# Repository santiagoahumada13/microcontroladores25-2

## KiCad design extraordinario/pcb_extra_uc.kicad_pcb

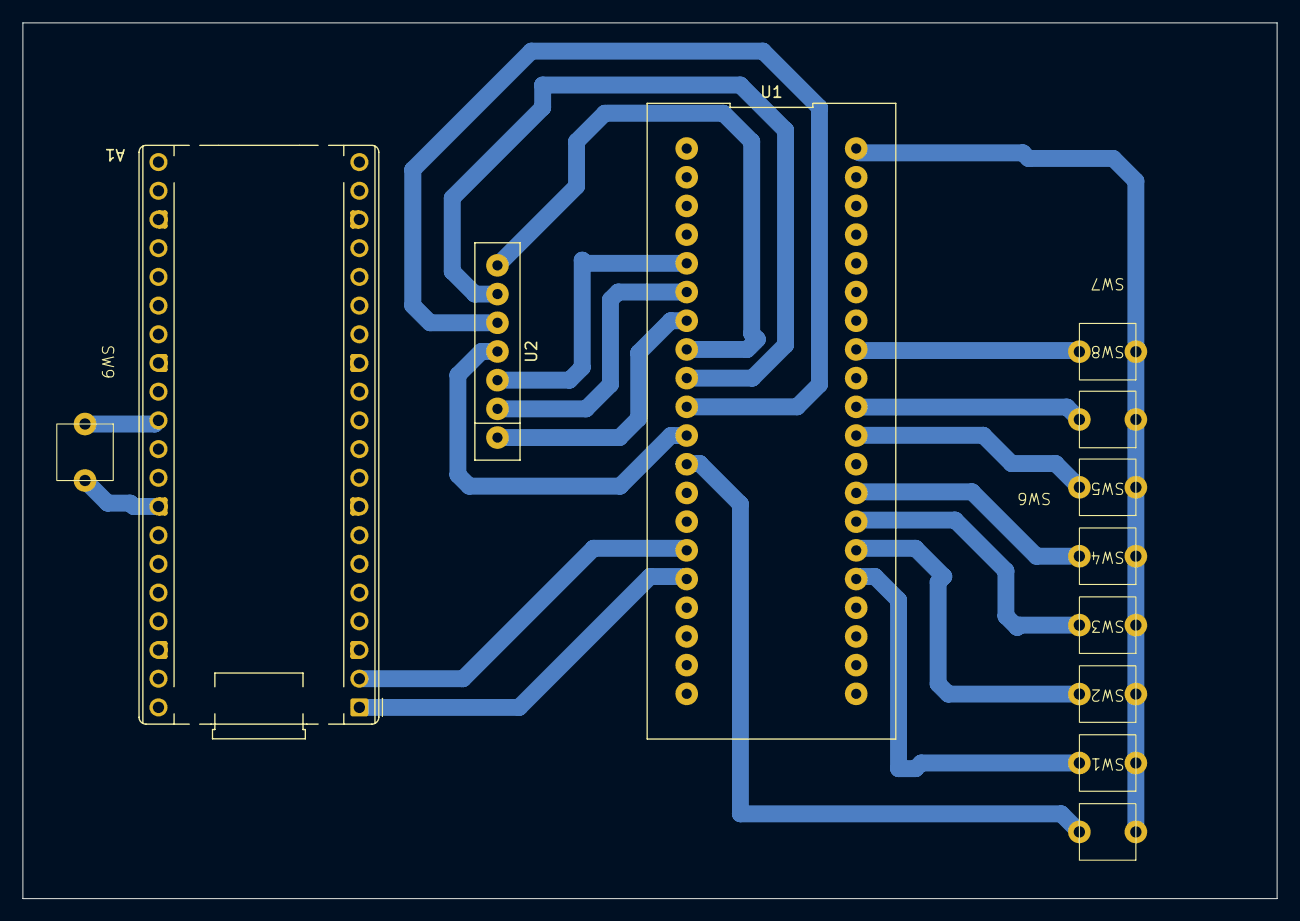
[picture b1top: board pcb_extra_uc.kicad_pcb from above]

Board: 2 copper layers, 111.0 x 77.5 mm, 12 parts (0 on the bottom side), 21 nets.

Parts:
A1: RaspberryPi_Pico_W; RaspberryPi_Pico_Common_THT
SW1, SW2, SW3, SW4, SW5, SW6, SW7, SW8, SW9: SW_Push; push_bttn2x1-tht
U1: STM32F104C8T6 BluePill
U2: keypad4x3

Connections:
unnamed: A1.33 (AGND), SW9.1
unnamed: A1.3 (GND), A1.8 (GND), A1.13 (GND), A1.18 (GND), A1.23 (GND), A1.28 (GND), A1.38 (GND)
unnamed: A1.1 (GPIO0), U1.16 (B11)
unnamed: A1.2 (GPIO1), U1.15 (B10)
unnamed: A1.30 (RUN), SW9.2
unnamed: SW1.2, SW2.2, SW3.2, SW4.2, SW5.2, SW6.2, SW7.2, SW8.2, U1.40 (3.3)
unnamed: U1.5 (A0), U2.3 (R3)
unnamed: U1.6 (A1), U2.2 (R2)
unnamed: U1.7 (A2), U2.1 (R1)
unnamed: U1.8 (A3), U2.7 (C3)
unnamed: U1.9 (A4), U2.6 (C2)
unnamed: U1.10 (A5), U2.5 (C1)
unnamed: U1.11 (A6), U2.4 (R4)
unnamed: SW1.1, U1.12 (A7)
unnamed: SW2.1, U1.25 (A8)
unnamed: SW3.1, U1.26 (A9)
unnamed: SW4.1, U1.27 (A10)
unnamed: SW5.1, U1.28 (A11)
unnamed: SW6.1, U1.30 (A15)
unnamed: SW8.1, U1.31 (B3)
unnamed: SW7.1, U1.33 (B5)

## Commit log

2025-04-01 ADC-PWM
